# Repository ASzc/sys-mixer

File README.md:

# SYS Mixer

The SYS Mixer is a conversion board for the SYS from Schitt Audio. It turns it
into a passive line-level audio mixer, rather than switching between the inputs
in a binary manner.

The pushbutton switch selects which channel the variable resistor attenuates.
Only one channel can be attenuated at one time, due the limitations of the
SYS's default control layout.

## Bill of Materials

Components required to populate the board:

| Qty  | Part | Description |
| ---- | ---- | ---- |
| 2 | Keystone 1790-3 | PCB Standoff, 4.75mm lift, 4-40 thread |
| 1 | Alps SPUN194700 | Pushbutton Switch, 4PDT, latching |
| 1 | Alps RK09712200MC | Potentiometer, 10 kOhms, 2 gang |
| 3 | CUI RCJ-2123 | RCA Jack, two port  |
| 4 | Vishay MRS25000C1002FCT00 | Resistor, 10 kOhms, thin film, 600 mW |

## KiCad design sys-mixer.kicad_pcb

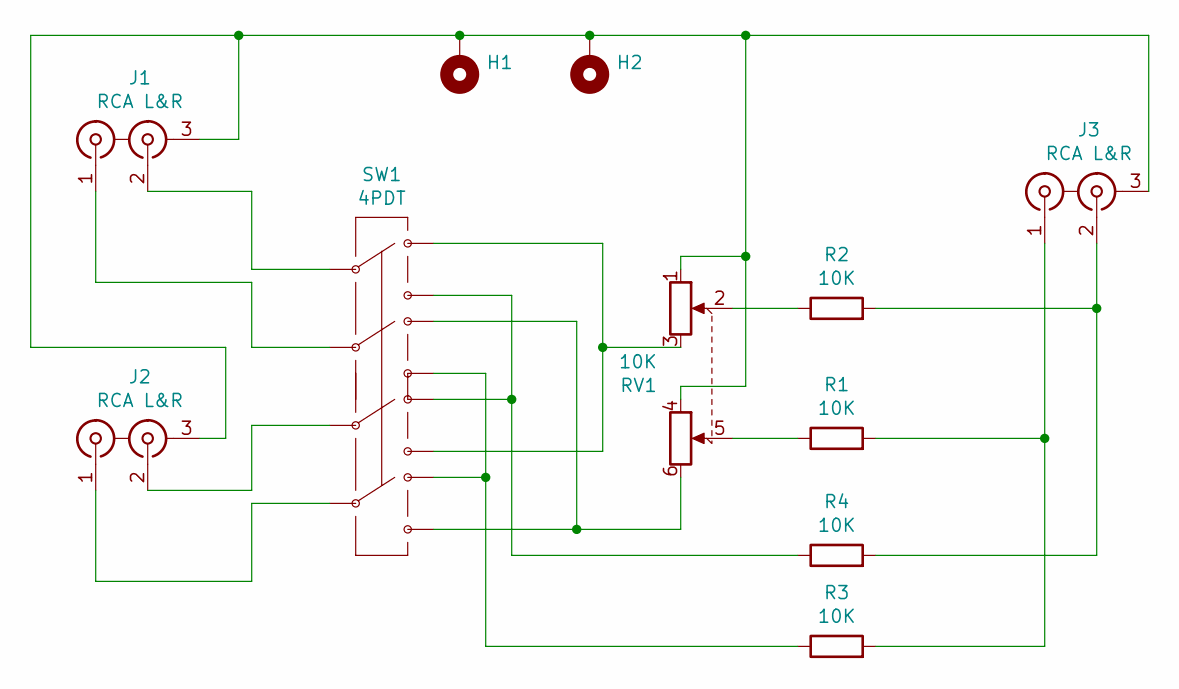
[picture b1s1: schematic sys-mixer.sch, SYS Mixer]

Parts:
H1, H2: MountingHole_Pad; MountingHole_4.9mm_Pad_Via
J1, J2, J3: RCA L&R; Coaxial-RCJ-2123
R1, R2, R3, R4: 10K; R_Axial_DIN0207_L6.3mm_D2.5mm_P10.16mm_Horizontal
RV1: 10K; POT-RK09712200MC
SW1: 4PDT; 4PDT-SPUN191400

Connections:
unnamed: H1.1, H2.1, J1.3 (EXT), J2.3 (EXT), J3.3 (EXT), RV1.1, RV1.4
unnamed: J1.1 (IN1), SW1.6
unnamed: J1.2 (IN2), SW1.3
unnamed: J2.1 (IN1), SW1.12
unnamed: J2.2 (IN2), SW1.9
unnamed: J3.1 (IN1), R1.2, R3.2
unnamed: J3.2 (IN2), R2.2, R4.2
unnamed: R1.1, RV1.5
unnamed: R2.1, RV1.2
unnamed: R3.1, SW1.5, SW1.10
unnamed: R4.1, SW1.2, SW1.7
unnamed: RV1.3, SW1.1, SW1.8
unnamed: RV1.6, SW1.4, SW1.11

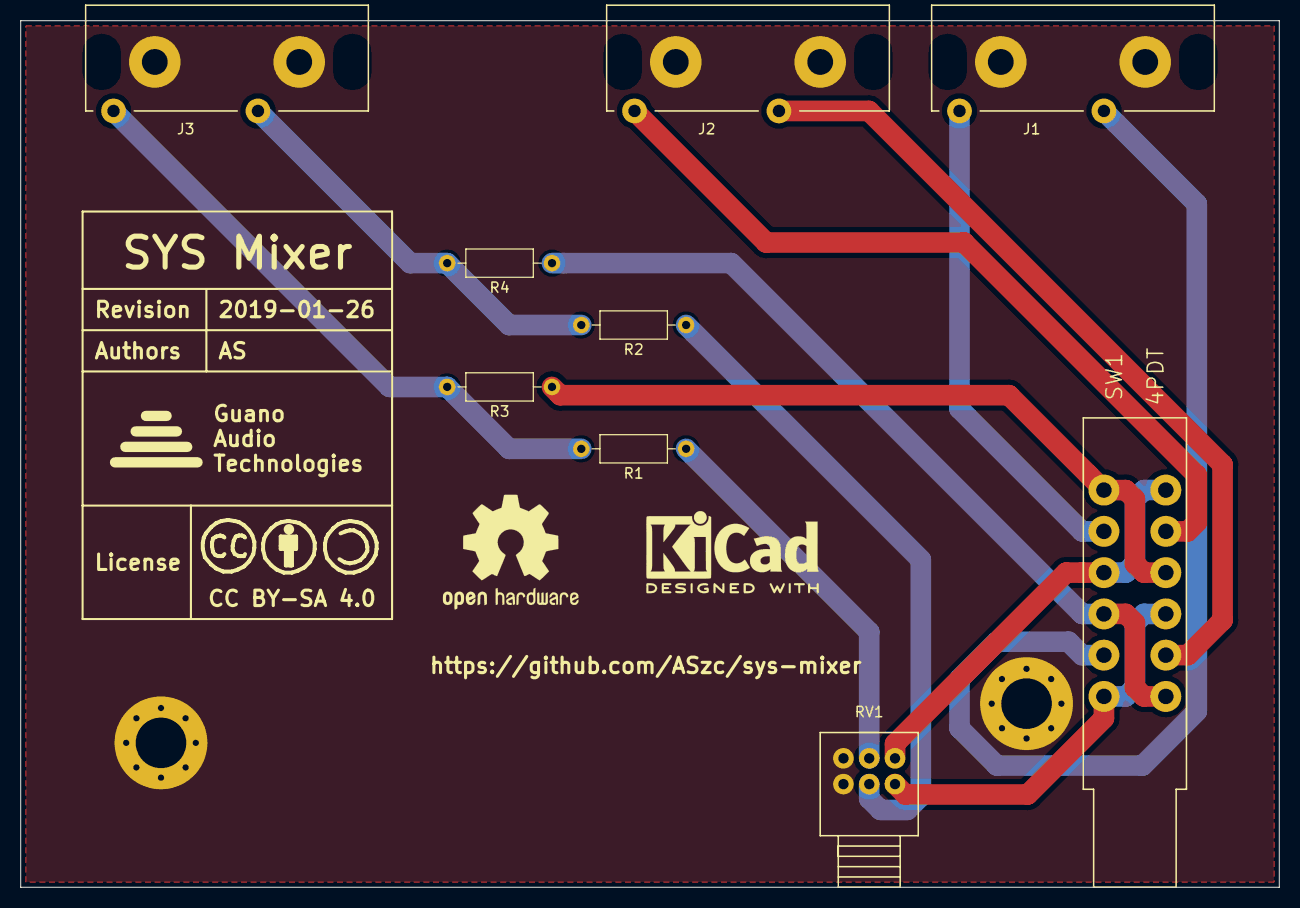
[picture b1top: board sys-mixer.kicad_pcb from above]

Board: 2 copper layers, 122.0 x 84.0 mm, 11 parts (0 on the bottom side), 13 nets.

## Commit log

2019-01-15 Initial version
2019-01-15 Add simple readme
2019-01-15 Add github URL to silkscreen
2019-01-15 Add components table to readme
2019-01-16 Reroute output so both channels are on B.Cu
    Also adjust silk info position
2019-01-27 Fix resistor position in schematic
    Having the resistors right after the inputs causes the mixing to
    misbehave.
    Also tweaked mounting hole and control positions, based on fitting of
    2019-01-15 boards.

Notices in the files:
sys-mixer.kicad_pcb:
CC BY-SA 4.0
